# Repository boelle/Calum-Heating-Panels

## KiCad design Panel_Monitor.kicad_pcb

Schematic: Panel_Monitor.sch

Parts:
D1: 1N4005; D_DO-15_P10.16mm_Horizontal
D2: GREEN; LED_D3.0mm
D3: RED; LED_D3.0mm
D4: ORANGE; LED_D3.0mm
J1: Raspberry_Pi_2_3; PinSocket_2x20_P2.54mm_Vertical
J2, J3, J4, J5: Conn_01x02; Angle Spade Connector
J6: Conn_01x02_Male; PinHeader_1x02_P2.54mm_Vertical
J7: Conn_01x03_Male; PinHeader_1x02_P2.54mm_Vertical
K1: G5LE-1; Relay_SPDT_Omron-G5LE-1
PS1: IRM-10-5; ACDC-Conv_THTMeanWell-IRM-02-XX
Q1: DS18B20; TO-92
Q2: 2N222A; TO-92
R1, R6: 10K; R_Axial_DIN0204_L3.6mm_D1.6mm_P5.08mm_Horizontal
R2, R5: 1K; R_Axial_DIN0204_L3.6mm_D1.6mm_P5.08mm_Horizontal
R3, R4, R7: 220; R_Axial_DIN0204_L3.6mm_D1.6mm_P5.08mm_Horizontal
SW1: Latching Button

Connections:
/3.3V: J1.1 (3V3), J1.17 (3V3), J7.3, Q1.3 (VDD), R1.1
/5V: D1.1 (K), J6.2, K1.2, R4.2, SW1.2
/GPIO4: J1.7 (GCLK0/GPIO4), J7.2, Q1.2 (DQ), R1.2
/GPIO17: J1.11 (GPIO17), R2.1
/GPIO22: J1.15 (GPIO22), R5.1, R6.1
/GPIO27: J1.13 (GPIO27), R3.2
GND: D2.1 (K), D4.1 (K), J1.6 (GND), J1.9 (GND), J1.14 (GND), J1.20 (GND), J1.25 (GND), J1.30 (GND), J1.34 (GND), J1.39 (GND), J6.1, J7.1, PS1.3 (-Vo), Q1.1 (GND), Q2.1 (E), R6.2
unnamed: D1.2 (A), D3.1 (K), K1.5, Q2.3 (C)
unnamed: D2.2 (A), R3.1
unnamed: D3.2 (A), R4.1
unnamed: D4.2 (A), R7.1
unnamed: J1.37 (GPIO26), R7.2
unnamed: J2.1, J2.2, J3.1, J3.2, PS1.1 (AC/N)
unnamed: J4.1, J4.2, K1.3
unnamed: J5.1, J5.2, K1.1, PS1.2 (AC/L)
unnamed: Q2.2 (B), R2.2
unnamed: R5.2, SW1.1

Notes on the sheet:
Connects to GPIO 4 / Pin 7

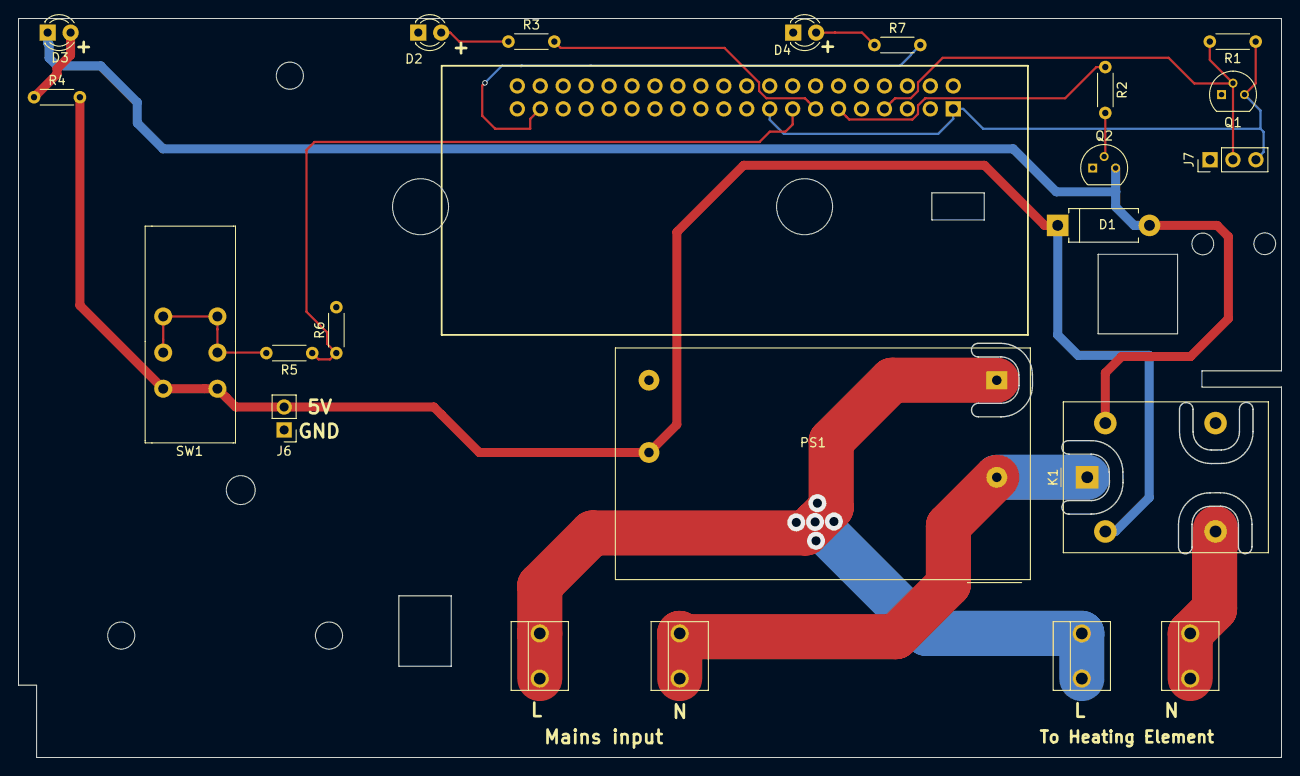
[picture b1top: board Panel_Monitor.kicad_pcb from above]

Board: 2 copper layers, 139.8 x 81.8 mm, 23 parts (0 on the bottom side), 17 nets.

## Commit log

2020-05-23 Cleaned up
2020-06-05 added holes for thermal cutout
2023-07-31 Update speed-emoncms.py
    added user agent
